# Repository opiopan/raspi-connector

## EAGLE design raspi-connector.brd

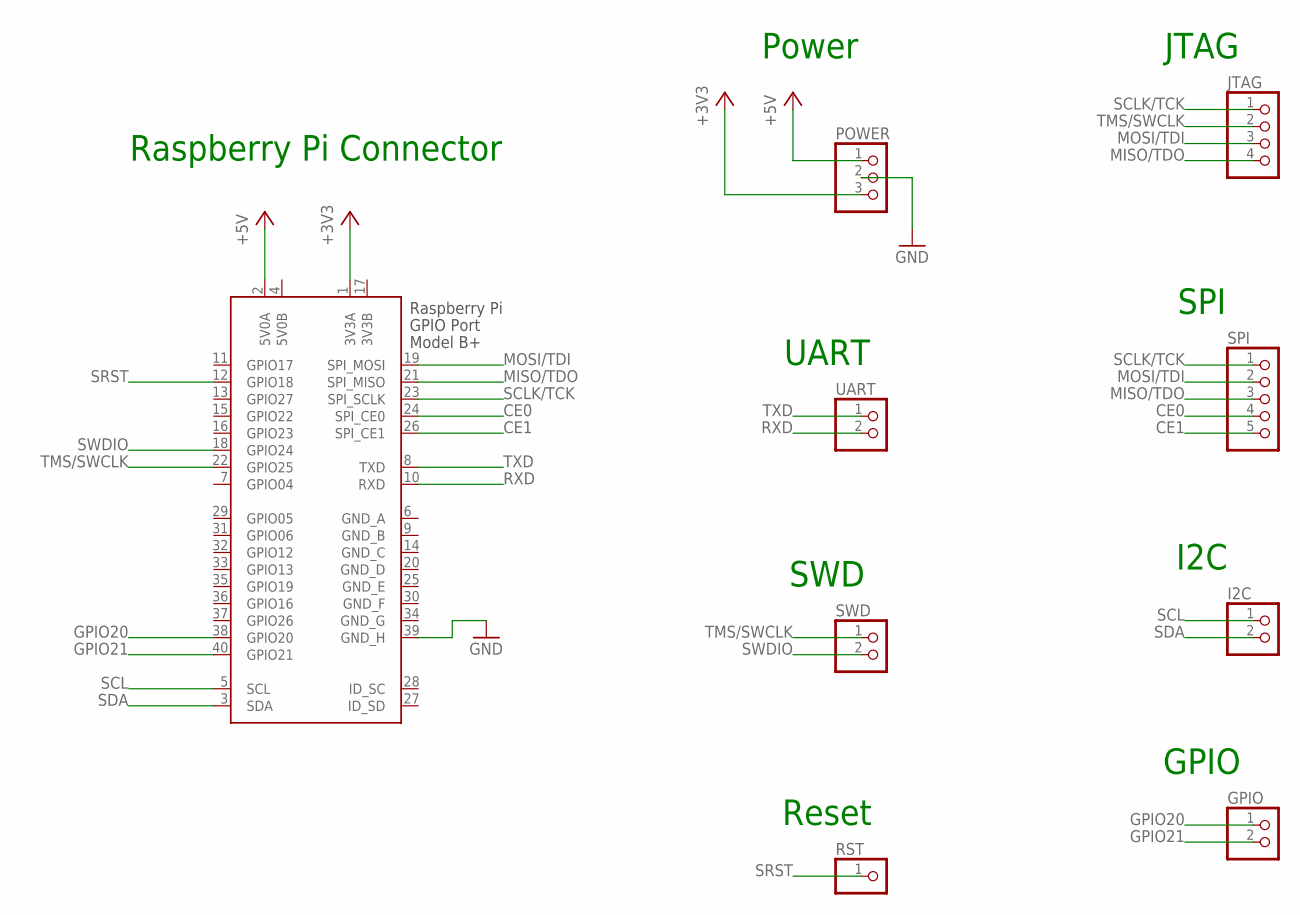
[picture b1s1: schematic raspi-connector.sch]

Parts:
GPIO: PINHD-1X2; 1X02
I2C: PINHD-1X2; 1X02
JTAG: PINHD-1X4; 1X04
POWER: PINHD-1X3; 1X03
RST: PINHD-1X1; 1X01
SPI: PINHD-1X5; 1X05
SWD: PINHD-1X2; 1X02
UART: PINHD-1X2; 1X02
X1: RASPI_BOARD_B+#; RASPI_BOARD_B+HAT_SMALL

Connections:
3V3B: X1.17 (3V3B)
5V0B: X1.4 (5V0B)
+3V3: POWER.3, X1.1 (3V3A)
+5V: POWER.1, X1.2 (5V0A)
CE0: SPI.4, X1.24 (SPI_CE0)
CE1: SPI.5, X1.26 (SPI_CE1)
GND: POWER.2, X1.39 (GND_H)
GND_A: X1.6 (GND_A)
GND_B: X1.9 (GND_B)
GND_C: X1.14 (GND_C)
GND_D: X1.20 (GND_D)
GND_E: X1.25 (GND_E)
GND_F: X1.30 (GND_F)
GND_G: X1.34 (GND_G)
GPIO20: GPIO.1, X1.38 (GPIO20)
GPIO21: GPIO.2, X1.40 (GPIO21)
MISO/TDO: JTAG.4, SPI.3, X1.21 (SPI_MISO)
MOSI/TDI: JTAG.3, SPI.2, X1.19 (SPI_MOSI)
RXD: UART.2, X1.10 (RXD)
SCL: I2C.1, X1.5 (SCL)
SCLK/TCK: JTAG.1, SPI.1, X1.23 (SPI_SCLK)
SDA: I2C.2, X1.3 (SDA)
SRST: RST.1, X1.12 (GPIO18)
SWDIO: SWD.2, X1.18 (GPIO24)
TMS/SWCLK: JTAG.2, SWD.1, X1.22 (GPIO25)
TXD: UART.1, X1.8 (TXD)

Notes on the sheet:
Raspberry Pi Connector
Power
UART
SWD
Reset
JTAG
SPI
I2C
GPIO

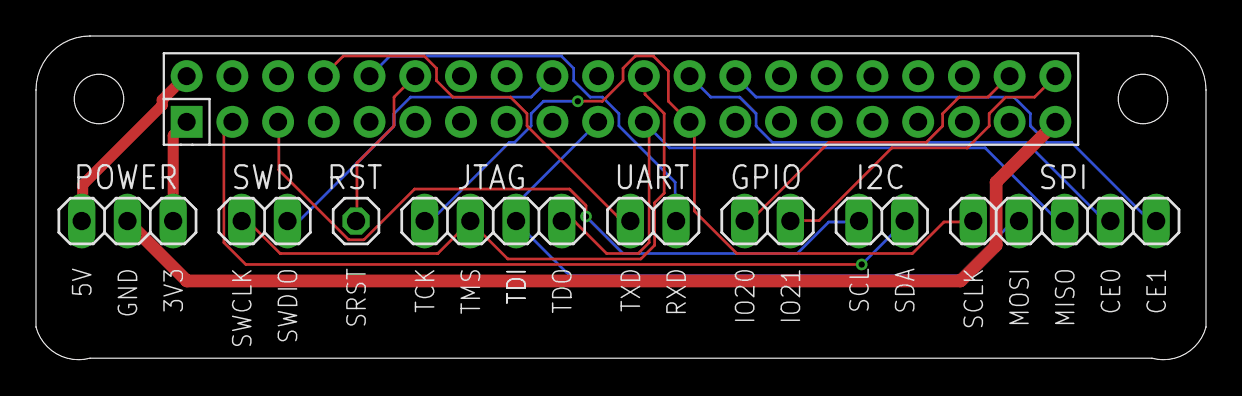
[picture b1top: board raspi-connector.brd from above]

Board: 2 copper layers, 65.0 x 18.0 mm, 9 parts (0 on the bottom side), 17 nets.
